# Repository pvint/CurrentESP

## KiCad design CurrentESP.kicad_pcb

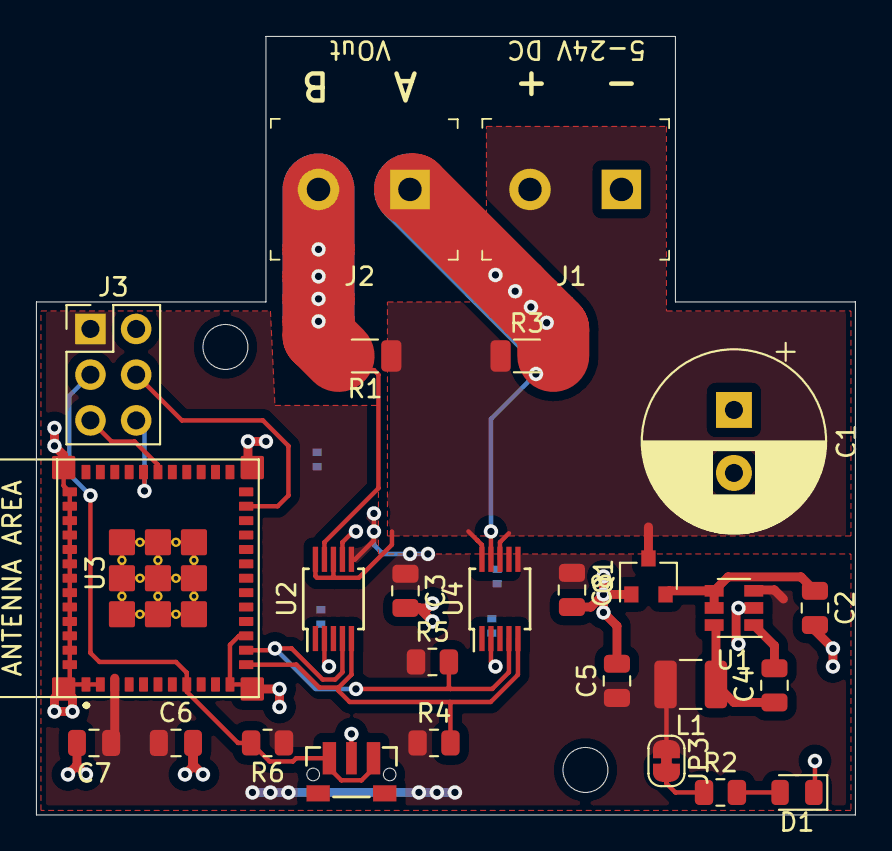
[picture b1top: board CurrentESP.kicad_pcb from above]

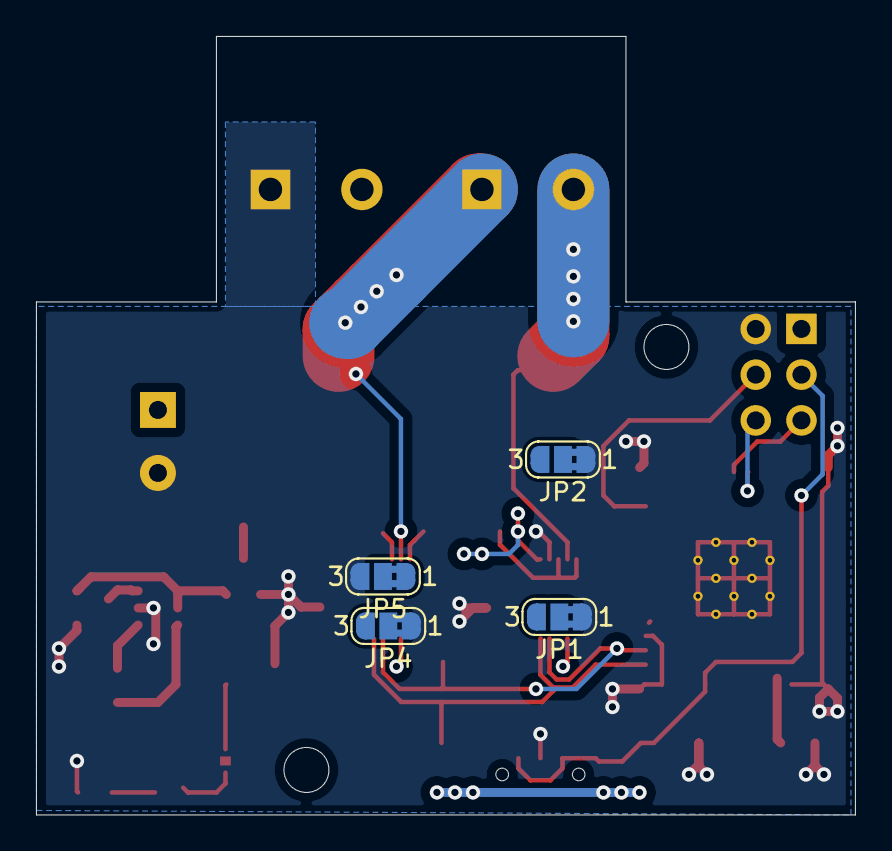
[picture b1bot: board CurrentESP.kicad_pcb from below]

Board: 2 copper layers, 45.5 x 43.2 mm, 30 parts (4 on the bottom side), 20 nets.

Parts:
C1: 47u; CP_Radial_D10.0mm_P3.50mm
C2: 2.2uF; C_0805_2012Metric
C3, C4, C7, C8: 0.1uF; C_0805_2012Metric
C5: 22uF; C_0805_2012Metric
C6: 10uF; C_0805_2012Metric
D1: LED RED; LED_0805_2012Metric
J1, J2: Screw_Terminal_01x02; Term_Block_1x2_P5.08MM
J3: Conn_02x03_Counter_Clockwise; PinHeader_2x03_P2.54mm_Vertical
JP1, JP2, JP4, JP5: SolderJumper_3_Bridged12; SolderJumper-3_P1.3mm_Bridged2Bar12_RoundedPad1.0x1.5mm_Num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
JP3: SolderJumper_2_Bridged; SolderJumper-2_P1.3mm_Bridged_RoundedPad1.0x1.5mm
L1: 10uH; L_1210_3225Metric
Q1: SSM3J340R; SOT-23
R1, R3: 5mΩ; R_1206_3216Metric
R2: 2.2k; R_0805_2012Metric
R4, R5, R6: 10k; R_0805_2012Metric
SW1: SW_Push; SW_TACTILE_PO21301
U1: TPS560430X3FDBVT; SOT-23-6
U2, U4: INA226; MSOP-10_3x3mm_P0.5mm
U3: esp32-c3-mini

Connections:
+3V3: C3.1, C5.1, C6.1, C7.1, C8.1, J3.1, JP1.3, JP2.3, JP3.1, JP4.3, JP5.1, L1.2, R4.1, R5.1, R6.1, U1.3, U2.6, U3.31, U4.6
+VDC: J1.2, Q1.3, R1.1, R3.1, U2.8, U2.10, U4.8, U4.10
BOOT: J3.4, U3.15
EN: J3.3, R6.2, SW1.1, U3.7
GND: C1.2, C2.2, C3.2, C5.2, C6.2, C7.2, C8.2, D1.1, J1.1, J3.2, JP1.1, JP2.1, JP4.1, JP5.3, Q1.1, SW1.2, U1.2, U2.7, U3.33, U4.7
unnamed: C4.1, L1.1, U1.6
unnamed: C4.2, U1.1
unnamed: D1.2, R2.2
unnamed: JP1.2, U2.1
unnamed: JP2.2, U2.2
unnamed: JP3.2, R2.1
unnamed: JP4.2, U4.1
unnamed: JP5.2, U4.2
Rx: J3.5, U3.27
SCL: R4.2, U2.5, U3.4, U4.5
SDA: R5.2, U2.4, U3.5, U4.4
SenseA-: J2.1, R3.2, U4.9
SenseB-: J2.2, R1.2, U2.9
Tx: J3.6, U3.28
Vin: C1.1, C2.1, Q1.2, U1.4, U1.5

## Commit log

2021-07-05 Basic layout done (not complete!)
